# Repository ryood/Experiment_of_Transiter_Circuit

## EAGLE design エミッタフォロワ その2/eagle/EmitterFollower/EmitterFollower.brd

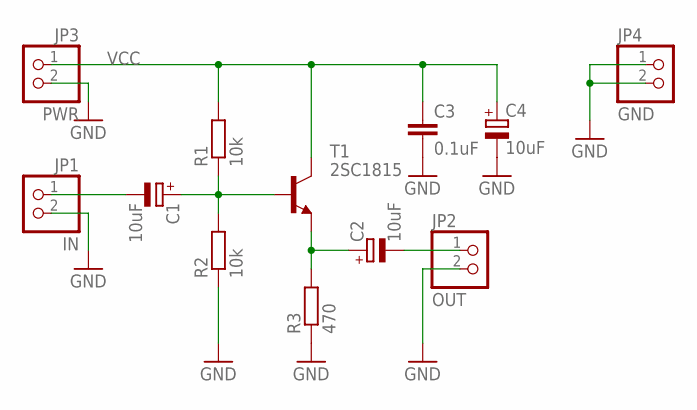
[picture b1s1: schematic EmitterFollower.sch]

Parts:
C1, C2, C4: 10uF; E2,5-6
C3: 0.1uF; C050-024X044
JP1: IN; 1X02
JP2: OUT; 1X02
JP3: PWR; 1X02
JP4: GND; 1X02
R1, R2: 10k; 0207/7
R3: 470; 0207/7
T1: 2SC1815; TO92-ECB

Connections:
GND: C3.2, C4.-, JP1.2, JP2.2, JP3.2, JP4.1, JP4.2, R2.1, R3.1
unnamed: C1.-, JP1.1
unnamed: C1.+, R1.1, R2.2, T1.B
unnamed: C2.-, JP2.1
unnamed: C2.+, R3.2, T1.E
VCC: C3.1, C4.+, JP3.1, R1.2, T1.C

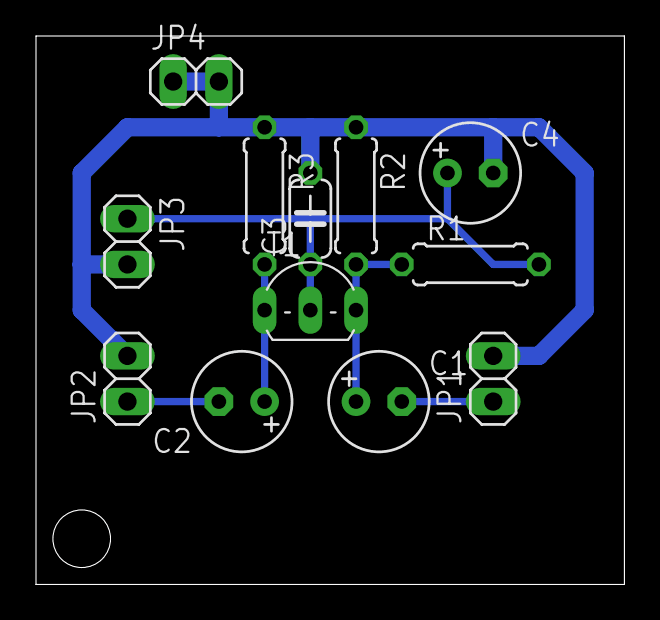
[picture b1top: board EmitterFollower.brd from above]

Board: 2 copper layers, 32.7 x 30.5 mm, 12 parts (0 on the bottom side), 6 nets.

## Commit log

2018-01-12 Add ベース接地回路
2018-01-17 Add カスコード回路、カスコード・ブートストラップ
2018-02-21 Add: 負帰還, 差動増幅回路
2018-03-22 Add:差動増幅回路 カスコード, カレントミラー シミュレーション
2018-06-09 カレントミラー、差動増幅回路 Tr2段
